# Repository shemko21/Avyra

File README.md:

Group Members and roles:

1. Dickson Mbogo - Program Developer
2. Elisha Jilo - Electrical Systems Developer
3. Shem Koech - Mechanical Designer
4. Masika - Supervisor

# Avyra
Overview
An autonomous ground-based robot designed to detect and fill potholes on roads using computer vision. It operates without human control by scanning surfaces, identifying damage, and performing targeted filling to restore road continuity.

Working

Surface Scanning
A forward-facing camera captures continuous images of the road ahead. These images are fed into a processing unit.

Pothole Detection
Using computer vision (OpenCV), the system analyzes the frames to detect depressions in the surface. Techniques include grayscale conversion, edge detection, contour analysis, and texture analysis to distinguish potholes from shadows or stains.

Classification
The identified area is validated against set thresholds for depth, size, and contrast to confirm it is a pothole. False positives are rejected.

Positioning
Once confirmed, the robot navigates precisely over the pothole using coordinate mapping and internal positioning logic. Navigation algorithms ensure accurate alignment.

Filling Operation
A concealed mechanism is activated to release and evenly spread filling material (e.g., asphalt mix or paste) into the pothole. The process is controlled to prevent overflow or underfill.

Surface Verification
A secondary image is captured post-fill. If the surface appears uniform and level, the robot resumes movement. If not, additional filling is triggered.

Loop Execution
The robot continues scanning and filling as it advances along the designated path.

Links:

Trello; https://trello.com/invite/b/684c2e9c0d75d9e9e22d4f1d/ATTI38f34ac70b7f9576e7ea711928b1238bC5E521BC/design-of-pothole-filling-robot-using-computer-vision

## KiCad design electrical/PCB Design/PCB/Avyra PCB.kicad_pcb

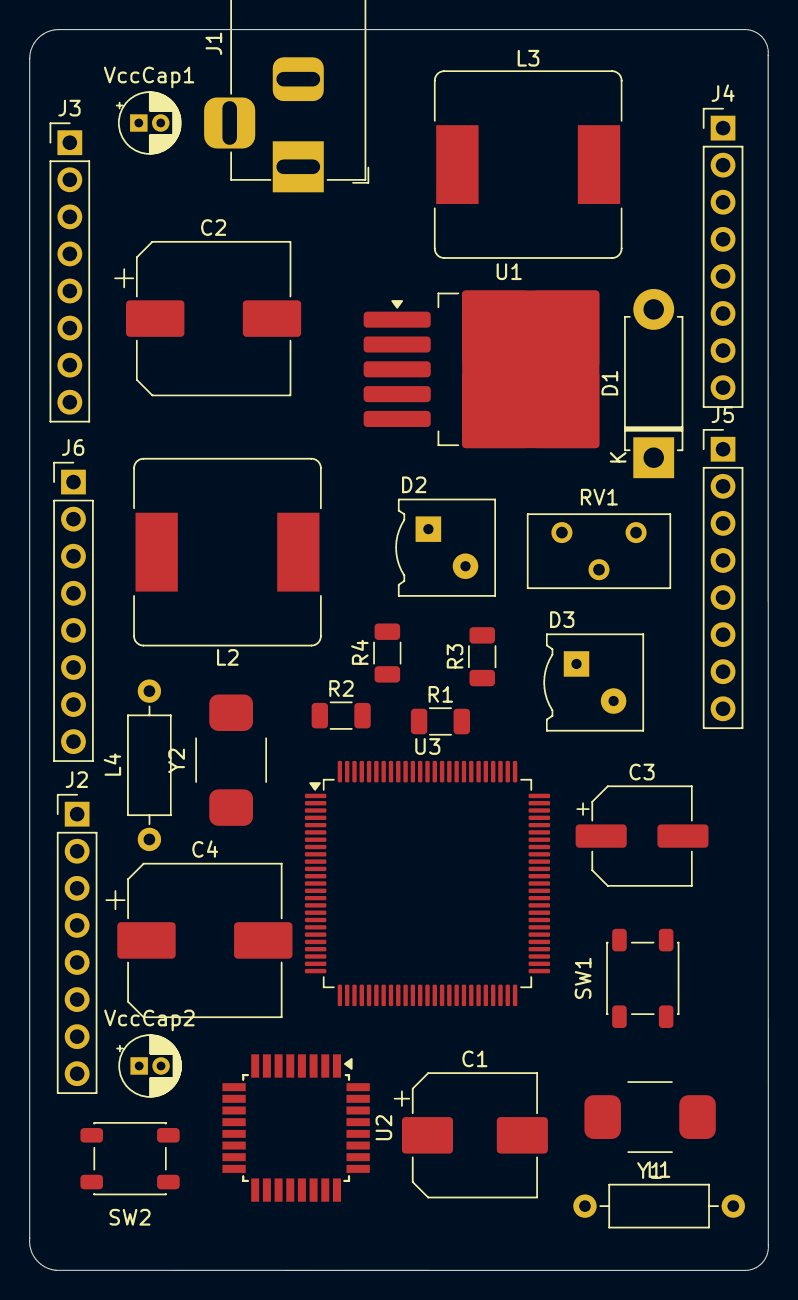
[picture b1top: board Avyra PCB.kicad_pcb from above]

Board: 2 copper layers, 50.6 x 85.0 mm, 31 parts (0 on the bottom side), 60 nets, no tracks yet.

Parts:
C1: 100u; CP_Elec_8x10
C2, C4: 220u; CP_Elec_10x10
C3: 100u; CP_Elec_6.3x5.4
D1: 1N5822; D_5W_P10.16mm_Horizontal
D2, D3: LED; LED_VCCLite_5381H1_6.35x6.35mm
J1: Barrel_Jack; BarrelJack_Horizontal
J2, J3: Conn_01x08_Pin; PinHeader_1x08_P2.54mm_Vertical
J4, J5, J6: Conn_01x15_Pin; PinHeader_1x08_P2.54mm_Vertical
L1, L4: L; L_Axial_L6.6mm_D2.7mm_P10.16mm_Horizontal_Vishay_IM-2
L2: 33 uH; L_Bourns_SRR1260
L3: 20 uH; L_Bourns_SRR1260
R1, R2, R3, R4: 1.21 k; R_1206_3216Metric
RV1: 50 k; Potentiometer_Bourns_3296Y_Vertical
SW1, SW2: SW_Push; SW_SPST_PTS647_Sx50
U1: LM2596S-ADJ; TO-263-5_TabPin3
U2: ATmega328-A; TQFP-32_7x7mm_P0.8mm
U3: ATmega2560-16A; TQFP-100_14x14mm_P0.5mm
VccCap1, VccCap2: C; CP_Radial_D4.0mm_P1.50mm
Y1, Y2: Crystal; Crystal_SMD_TXC_AX_8045-2Pin_8.0x4.5mm

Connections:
+5V: C3.1, L1.1, L3.2, L4.1, U2.4 (VCC), U2.6 (VCC), U3.10 (VCC), U3.31 (VCC), U3.61 (VCC), U3.80 (VCC), VccCap1.2, VccCap2.2
GND: C1.2, C2.2, C3.2, C4.2, D1.2 (A), D2.1 (K), D3.1 (K), J1.2, R1.2, SW1.2, SW2.2, U1.3 (GND), U1.5 (~ON/OFF), U2.3 (GND), U2.5 (GND), U2.21 (GND), U3.11 (GND), U3.32 (GND), U3.62 (GND), U3.81 (GND), U3.99 (GND), VccCap1.1, VccCap2.1
unnamed: C2.1, L2.2, L3.1, RV1.1
unnamed: D1.1 (K), L2.1, U1.2 (OUT)
unnamed: D2.2 (A), U2.17 (PB5)
unnamed: D3.2 (A), R4.2
unnamed: J2.1, U2.8 (XTAL2/PB7)
unnamed: J2.2, U2.23 (PC0)
unnamed: J2.3, U2.24 (PC1)
unnamed: J2.4, U2.25 (PC2)
unnamed: J2.5, U2.26 (PC3)
unnamed: J2.6, U2.27 (PC4)
unnamed: J2.7, U2.28 (PC5)
unnamed: J2.8, U2.29 (~RESET/PC6)
unnamed: J3.1, U2.30 (PD0)
unnamed: J3.2, U2.31 (PD1)
unnamed: J3.3, U2.32 (PD2)
unnamed: J3.4, U2.1 (PD3)
unnamed: J3.5, U2.2 (PD4)
unnamed: J3.6, U2.9 (PD5)
unnamed: J3.7, U2.10 (PD6)
unnamed: J3.8, U2.11 (PD7)
unnamed: J4.1, U3.78 (PA0)
unnamed: J4.2, U3.77 (PA1)
unnamed: J4.3, U3.76 (PA2)
unnamed: J4.4, U3.75 (PA3)
unnamed: J4.5, U3.74 (PA4)
unnamed: J4.6, U3.73 (PA5)
unnamed: J4.7, U3.72 (PA6)
unnamed: J4.8, U3.71 (PA7)
unnamed: J5.1, U3.26 (PB7)
unnamed: J5.2, U3.53 (PC0)
unnamed: J5.3, U3.54 (PC1)
unnamed: J5.4, U3.55 (PC2)
unnamed: J5.5, U3.56 (PC3)
unnamed: J5.6, U3.57 (PC4)
unnamed: J5.7, U3.58 (PC5)
unnamed: J5.8, U3.59 (PC6)
unnamed: J6.1, U3.3 (PE1)
unnamed: J6.2, U3.4 (PE2)
unnamed: J6.3, U3.5 (PE3)
unnamed: J6.4, U3.6 (PE4)
unnamed: J6.5, U3.7 (PE5)
unnamed: J6.6, U3.8 (PE6)
unnamed: J6.7, U3.9 (PE7)
unnamed: J6.8, U3.97 (PF0)
unnamed: R1.1, RV1.3
unnamed: R2.2, SW1.1
unnamed: R3.2, SW2.1
unnamed: RV1.2, U1.4 (FB)
unnamed: C1.1, J1.1, U1.1 (VIN)
unnamed: L1.2, U2.18 (AVCC)
unnamed: U2.12 (PB0), Y1.2
unnamed: U2.13 (PB1), Y1.1
unnamed: R2.1, U2.7 (XTAL1/PB6)
unnamed: L4.2, U3.100 (AVCC)
unnamed: U3.89 (PK0), Y2.2
unnamed: U3.88 (PK1), Y2.1
unnamed: R4.1, U3.35 (PL0)
unnamed: C4.1, R3.1, U3.30 (~RESET)

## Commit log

2025-06-17 Add base folder structure and README
2025-06-17 Add mechanical CAD and reference image
2025-06-18 electrical
2025-06-18 Upload proposal Docx
2025-06-18 updated proposal
2025-06-18 Create Template
2025-06-22 Pushed template
2025-06-23 Create init
2025-06-23 Uploaded PCB Design
